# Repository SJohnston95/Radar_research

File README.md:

# Radar_research
Here's the github for my radar research project

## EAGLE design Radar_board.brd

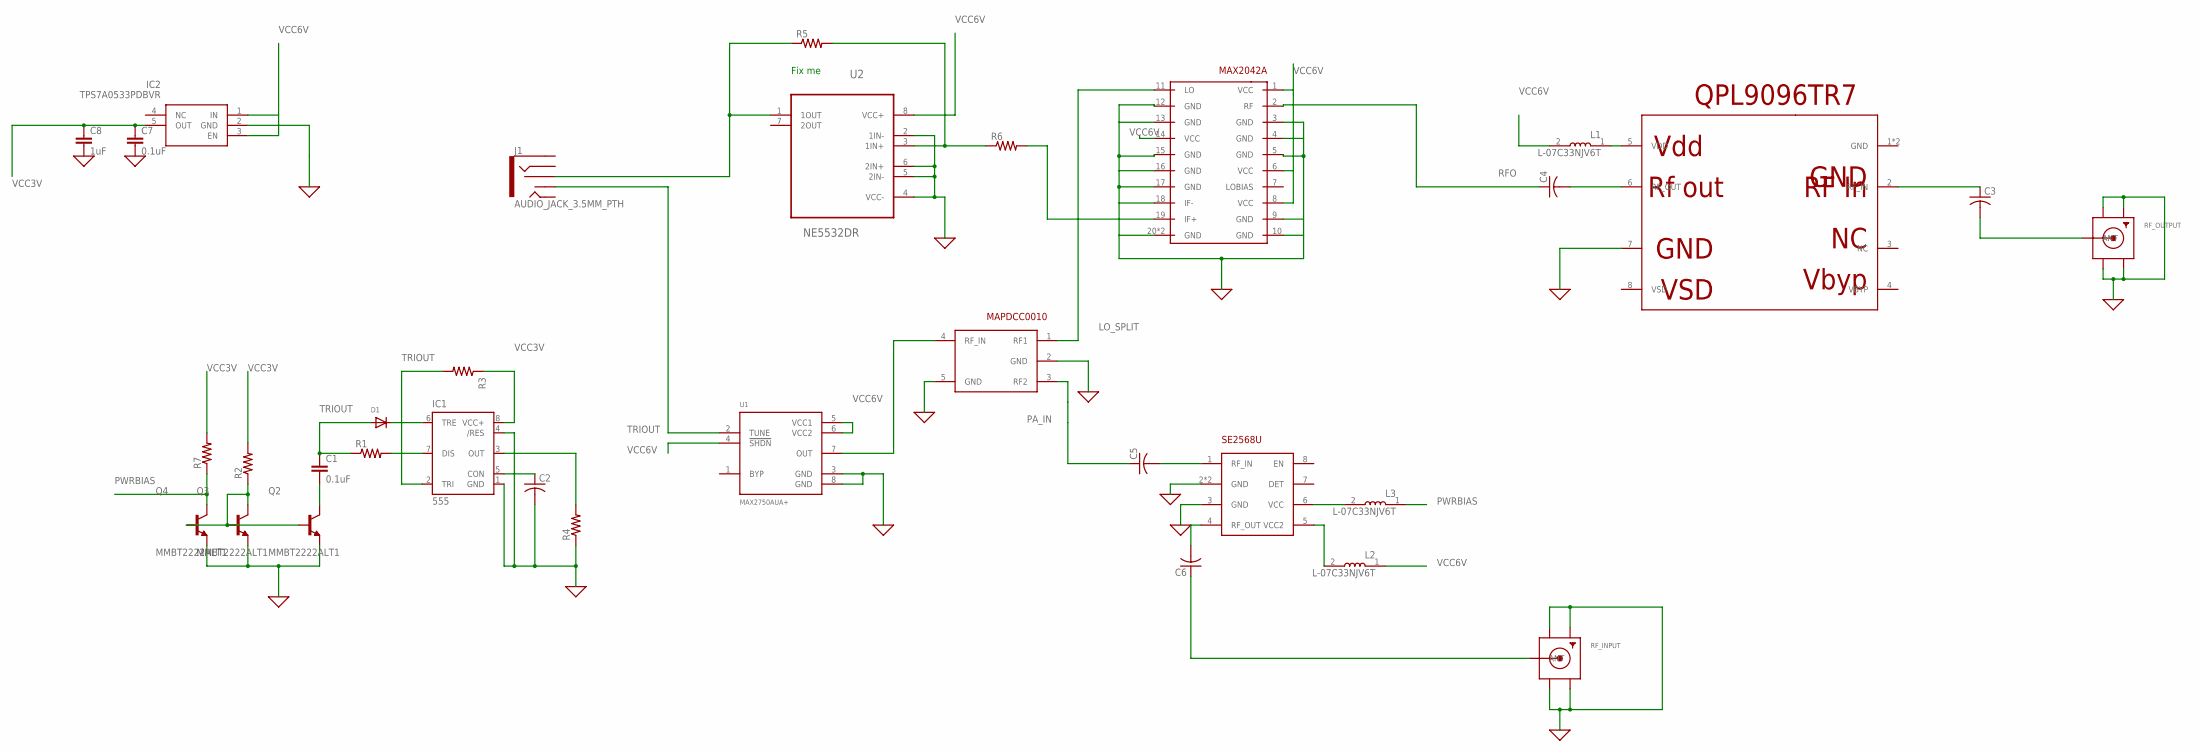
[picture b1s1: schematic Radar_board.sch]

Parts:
C1, C7: 0.1uF; 0402-CAP
C2: C-USC0603; C0603
C3, C4, C5, C6: C-USC0805; C0805
C8: 1uF; 0402-CAP
D1: DIODE_SOD-123FL; SOD-123FL
IC1: 555; SO08
IC2: TPS7A0533PDBVR; SOT95P280X145-5N
J1: AUDIO_JACK_3.5MM_PTH; AUDIO-JACK
L1, L2, L3: L-07C33NJV6T; INDC1005X60N
Q2, Q3, Q4: MMBT2222ALT1; SOT95P237X111-3N
R1, R2, R3, R4, R5, R6, R7: R-US_R0603; R0603
RF_INPUT: SMACONNECTOR_EDGE; SMA_EDGELAUNCH
RF_OUTPUT: SMACONNECTOR_EDGE; SMA_EDGELAUNCH
U1: MAX2750AUA+; SOP65P490X110-8N
U2: NE5532DR; SOIC127P600X175-8N
U$1: QPL9096TR7DFT-8; SON50P202X202X80-9T80X160
U$2: MAX2042AT2055; QFN65P500X500X80-21T310
U$3: SE2568UDFN8; SON50P202X202X80-9T80X160
U$4: MAPDCC0010SOT-25; SOT95P284X110-5

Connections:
GND: C2.2, C7.2, C8.2, IC1.1 (GND), IC1.4 (/RES), IC2.2 (GND), Q2.2 (E), Q3.2 (E), Q4.2 (E), R4.1, RF_INPUT.GND@1 (GND4), RF_INPUT.GND@2 (GND3), RF_INPUT.GND@3 (GND2), RF_INPUT.GND@4 (GND1), RF_OUTPUT.GND@1 (GND4), RF_OUTPUT.GND@2 (GND3), RF_OUTPUT.GND@3 (GND2), RF_OUTPUT.GND@4 (GND1), U1.3 (GND), U1.8 (GND), U2.2 (1IN-), U2.4 (VCC-), U2.5 (2IN-), U2.6 (2IN+), U$1.7, U$2.3 (GND), U$2.4 (GND), U$2.5 (GND), U$2.9 (GND), U$2.10 (GND), U$2.12 (GND), U$2.13 (GND), U$2.15 (GND), U$2.16 (GND), U$2.17 (GND), U$2.18 (IF-), U$2.20 (GND), U$2.21 (GND), U$3.2 (GND), U$3.3 (GND), U$3.9 (GND), U$4.2 (GND), U$4.5 (GND)
LO: U1.7 (OUT), U$4.4 (RF_IN)
LO_SPLIT: U$2.11 (LO), U$4.1 (RF1)
unnamed: Q2.1 (B), Q3.1 (B), Q3.3 (C), Q4.1 (B), R2.1
unnamed: C1.2, Q2.3 (C)
unnamed: IC1.7 (DIS), R1.2
unnamed: IC1.3 (OUT), R4.2
unnamed: C2.1, IC1.5 (CON)
unnamed: D1.C, IC1.6 (TRE)
unnamed: L2.2, U$3.5 (VCC2)
unnamed: C3.1, U$1.2 (RF_IN)
unnamed: L1.1, U$1.5 (VDD)
unnamed: C3.2, RF_OUTPUT.P (ANT)
unnamed: C5.2, U$3.1 (RF_IN)
unnamed: C6.2, U$3.4 (RF_OUT)
unnamed: C4.2, U$1.6 (RF_OUT)
unnamed: C6.1, RF_INPUT.P (ANT)
unnamed: J1.RSH, R5.1, U2.1 (1OUT)
unnamed: R5.2, R6.1, U2.3 (1IN+)
PA_IN: C5.1, U$4.3 (RF2)
PWRBIAS: L3.1, Q4.3 (C), R7.1
RFO: C4.1, U$2.2 (RF)
TRIOUT: C1.1, D1.A, IC1.2 (TRI), J1.TSH, R1.1, R3.2, U1.2 (TUNE)
TV_IN: R6.2, U$2.19 (IF+)
VCC1V: L3.2, U$3.6 (VCC)
VCC3V: C7.1, C8.1, IC1.8 (VCC+), IC2.5 (OUT), R2.2, R3.1, R7.2
VCC6V: IC2.1 (IN), IC2.3 (EN), L1.2, L2.1, U1.4 (!SHDN), U1.5 (VCC1), U1.6 (VCC2), U2.8 (VCC+), U$2.1 (VCC), U$2.6 (VCC), U$2.8 (VCC), U$2.14 (VCC)

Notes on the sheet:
Fix me

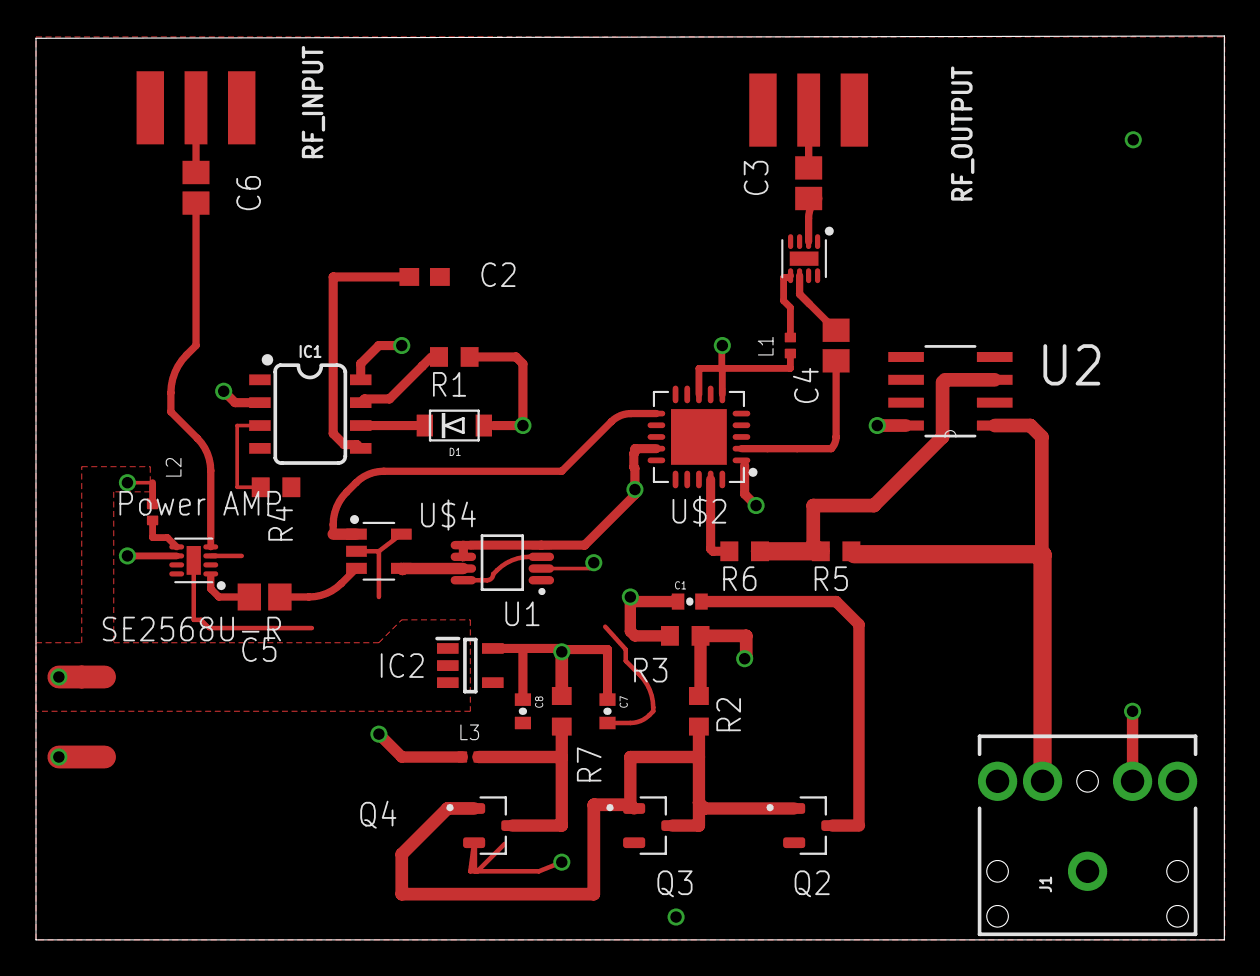
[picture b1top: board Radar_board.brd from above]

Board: 4 copper layers, 66.0 x 50.2 mm, 33 parts (0 on the bottom side), 27 nets.

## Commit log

2019-06-10 Layout and original concept
    Here's my initial files for this project. Right now I"m working on a layout for my board. I've completed my relaxation oscillator design and then I'm working on building a board capable of transmitti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
2019-08-17 Board update and GBR files for printing
2019-08-19 SAR Analysis code
    Non working skeleton code. The first of many updates.

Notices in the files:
parts and their libraries:
SparkFun-Retired: Licensing: Creative Commons ShareAlike 4.0 International - https://creativecommons.org/licenses/by-sa/4.0
